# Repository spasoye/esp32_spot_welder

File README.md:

# ESP32 DIY Spot Welder Controller

A precision pulse controller for building a spot welder from a microwave oven transformer (MOT). Features configurable timing, safety controls, and an intuitive rotary encoder interface.

## ⚡ What It Does

Converts a dangerous MOT into a safe, controllable spot welder for battery tab welding, metalworking projects, and electronics repair. The ESP32 generates precise current pulses while the solid-state relay handles the high-power switching safely.

## 🎯 Key Features

- **Configurable pulse timing** - Adjust ON/OFF duration and pulse count via rotary encoder
- **Safety-critical design** - Software-controlled SSR prevents accidental activation
- **Real-time feedback** - 16x2 LCD shows current settings and pulse count
- **Precise control** - Microsecond-level timing for consistent welds
- **Easy interface** - Rotary encoder for parameter adjustment without recompilation

## 🔧 Hardware Requirements

- ESP32 development board
- 16x2 I2C LCD display (HD44780-compatible)
- Rotary encoder
- Solid state relay (SSR) rated for mains voltage
- Microwave oven transformer (MOT)
- Foot pedal or momentary switch (trigger)
- Power supply (3.3V/5V for ESP32, mains for MOT)

**⚠️ Safety Warning:** MOTs output extremely high current (1000+ amps). Improper construction can be lethal. Only attempt if you understand high-voltage/high-current safety practices.

## 📐 Circuit Diagram

Schematics available in `/kicad` directory. Key connections:
- ESP32 GPIO → SSR control input
- SSR output → MOT primary winding
- Rotary encoder → ESP32 GPIO (with debouncing)
- LCD → ESP32 I2C bus
- Trigger switch → ESP32 GPIO (with pull-up)

## 🚀 Building & Flashing

### Prerequisites
- ESP-IDF v4.x or later
- Git

### Clone with submodules
```bash
git clone --recursive https://github.com/spasoye/esp32_spot_welder.git
cd esp32_spot_welder/firmware
```

### Build and flash (choose one method)

**Using idf.py (recommended):**
```bash
idf.py build
idf.py -p /dev/ttyUSB0 flash monitor
```

**Using legacy make:**
```bash
make all -j8
make flash
```

## 🎮 Operation

1. **Power on** - LCD displays current pulse settings
2. **Adjust parameters** using rotary encoder:
   - Pulse ON time (milliseconds)
   - Pulse OFF time (milliseconds)  
   - Number of pulses (1-10)
3. **Press trigger** (foot pedal/switch) - LED indicates welding in progress
4. **Release trigger** - System returns to idle state

## 📊 Technical Highlights

- **ESP-IDF framework** - Professional-grade embedded development
- **Hardware timer control** - Precise pulse generation independent of task scheduling
- **Interrupt-driven encoder** - Responsive UI without polling overhead
- **I2C LCD library** - Clean abstraction using [esp32-i2c-lcd1602](https://github.com/DavidAntliff/esp32-i2c-lcd1602)
- **State machine design** - Safe mode transitions prevent accidental activation

## 📝 Configuration

Edit `main/config.h` to customize:
- GPIO pin assignments
- Default pulse parameters
- LCD I2C address
- Encoder sensitivity

## 🔗 Dependencies

- [esp32-i2c-lcd1602](https://github.com/DavidAntliff/esp32-i2c-lcd1602) - LCD display driver (included as submodule)

See [CHANGELOG.md](CHANGELOG.md) for version history.

## ⚠️ Disclaimer

This project involves high voltage and high current electricity. The author assumes no responsibility for injury, death, or property damage resulting from construction or use of this device. Build at your own risk.

## 📄 License

MIT License - See LICENSE file for details

---

**Built by Ivan Spasić** | [Portfolio](https://spas-tech.hr) | [GitHub](https://github.com/spasoye)

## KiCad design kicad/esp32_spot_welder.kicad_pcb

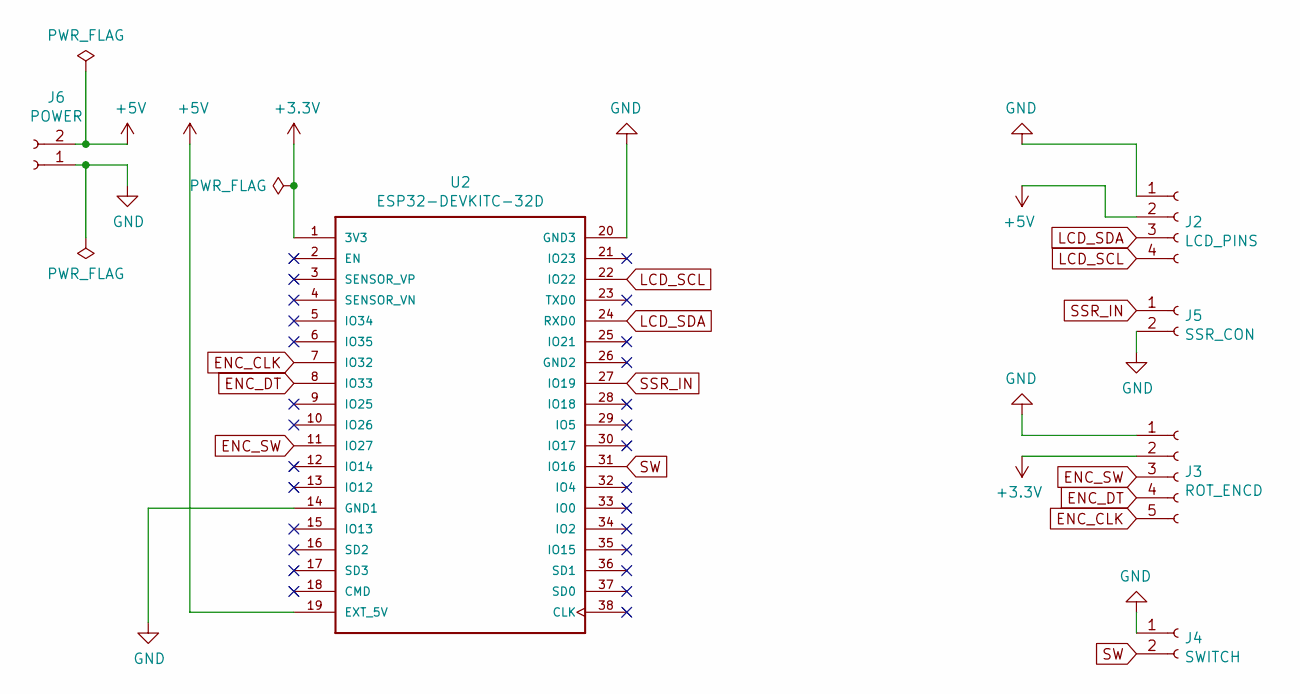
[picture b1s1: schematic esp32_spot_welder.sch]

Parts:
J2: LCD_PINS; PinHeader_1x04_P2.00mm_Vertical
J3: ROT_ENCD; PinHeader_1x05_P2.00mm_Vertical
J4: SWITCH; TerminalBlock_Philmore_TB132_1x02_P5.00mm_Horizontal
J5: SSR_CON; TerminalBlock_Philmore_TB132_1x02_P5.00mm_Horizontal
J6: POWER; TerminalBlock_Philmore_TB132_1x02_P5.00mm_Horizontal
U2: ESP32-DEVKITC-32D; MODULE_ESP32-DEVKITC-32D

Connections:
+3V3: J3.2, U2.1 (3V3)
+5V: J2.2, J6.2, U2.19 (EXT_5V)
ENC_CLK: J3.5, U2.7 (IO32)
ENC_DT: J3.4, U2.8 (IO33)
ENC_SW: J3.3, U2.11 (IO27)
GND: J2.1, J3.1, J4.1, J5.2, J6.1, U2.14 (GND1), U2.20 (GND3)
LCD_SCL: J2.4, U2.22 (IO22)
LCD_SDA: J2.3, U2.24 (RXD0)
SSR_IN: J5.1, U2.27 (IO19)
SW: J4.2, U2.31 (IO16)

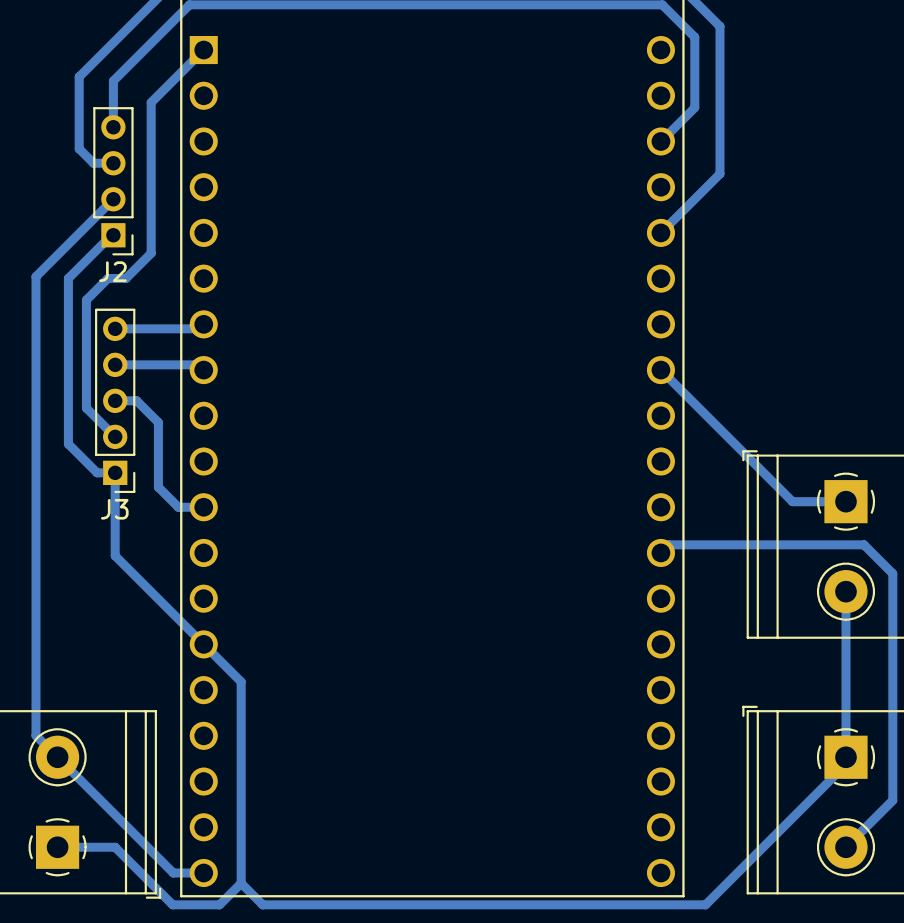
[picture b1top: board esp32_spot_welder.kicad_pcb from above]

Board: 2 copper layers, 6 parts (0 on the bottom side), 10 nets.

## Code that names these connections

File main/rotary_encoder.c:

#include <math.h>
#include <driver/gpio.h>
#include "freertos/FreeRTOS.h"
#include "freertos/task.h"
#include "freertos/queue.h"
#include "rotary_encoder.h"

#include "lcd.h"

#define ENC_CLK     GPIO_NUM_32
#define ENC_DT      GPIO_NUM_33
#define ENC_SW      27

static QueueHandle_t p_encoder_queue = NULL;
static int16_t duration = 100;

/**
 * @brief  Rotary encoder interrupt service routine. 
 * @note   Debounce protocol should be done here.
 * @param  *arg: pin that triggered the interrupt.
 * @retval None
 */
static void IRAM_ATTR encoder_isr_handler(void *arg);

/**
 * @brief  Task routine that haqndles interrupt events.
 * @note   None.
 * @param  *arg: task arguments. None in this case.
 * @retval None
 */
static void rotary_encoder_task(void *arg);

uint8_t rotary_encoder_init(void)
{
    gpio_config_t io_conf;
    uint8_t ret = 1;

    io_conf.intr_type = GPIO_PIN_INTR_DISABLE;
    io_conf.mode = GPIO_MODE_INPUT;
    io_conf.pin_bit_mask = (1ULL<<ENC_CLK);
    io_conf.pull_down_en = GPIO_PULLDOWN_DISABLE;
    io_conf.pull_up_en = GPIO_PULLDOWN_DISABLE;
    gpio_config(&io_conf);

    io_conf.intr_type = GPIO_PIN_INTR_NEGEDGE;
    io_conf.pin_bit_mask = (1ULL<<ENC_DT);
    io_conf.mode = GPIO_MODE_INPUT;
    io_conf.pull_up_en = GPIO_PULLDOWN_DISABLE;
    io_conf.pull_down_en = GPIO_PULLDOWN_DISABLE;
    gpio_config(&io_conf);

    io_conf.intr_type = GPIO_PIN_INTR_NEGEDGE;
    io_conf.pin_bit_mask = (1<<ENC_SW);
    io_conf.mode = GPIO_MODE_INPUT;
    io_conf.pull_up_en = GPIO_PULLDOWN_DISABLE;
    io_conf.pull_down_en = GPIO_PULLDOWN_DISABLE;
    gpio_config(&io_conf);

    gpio_install_isr_service(0);
    gpio_isr_handler_add(ENC_CLK, encoder_isr_handler, (void*)ENC_CLK);
    gpio_isr_handler_add(ENC_DT, encoder_isr_handler, (void*)ENC_DT);
    gpio_isr_handler_add(ENC_SW, encoder_isr_handler, (void*)ENC_SW);

    p_encoder_queue = xQueueCreate(1, sizeof(encoder_event_t));

    ret = (pdPASS ==xTaskCreatePinnedToCore(rotary_encoder_task, "rotary_encoder_task", 2048, NULL, 10, NULL, 0)) ? 0 : 1;

    return ret;
}

void rotary_encoder_int_disable(void)
{
    gpio_intr_disable(ENC_CLK);
    gpio_intr_disable(ENC_DT);
    gpio_intr_disable(ENC_SW);
}

void rotary_encoder_int_enable(void)
{
    gpio_intr_enable(ENC_CLK);
    gpio_intr_enable(ENC_DT);
    gpio_intr_enable(ENC_SW);
}

static void rotary_encoder_task(void *arg)
{
    encoder_event_t encod_val;
    uint8_t digit_pos = 0;
    uint8_t cursor_pos[] = {4, 1};

    lcd_set_dur(duration);
    lcd_user_pointer(cursor_pos);

    while(true)
    {
        if (xQueueReceive(p_encoder_queue, &encod_val, portMAX_DELAY))
        {
            printf("Interrupt from %d\n", encod_val);
            switch (encod_val)
            {
            case CLICK:
                digit_pos = (digit_pos+1)%4;
                cursor_pos[0] = 4-digit_pos;
                printf("Digit: %d\n", digit_pos);
                lcd_user_pointer(cursor_pos);
                break;

            case CCW:
                printf("-\n");
                duration = duration - pow(10, digit_pos);
                break;

            case CW:
                printf("+\n");
                duration = duration + pow(10, digit_pos);
                break;

            default:
                break;
            }
            
            // Value can't be smaller than 0;
            if (duration < 0)
            {
                duration = 0;
            }

            // Value can't be larger than 5000 ms.
            if (duration > 5000)
            {
                duration = 5000;
            }

            lcd_set_dur(duration);
            vTaskDelay(60/portTICK_PERIOD_MS);
            gpio_intr_enable(ENC_DT);
            gpio_intr_enable(ENC_SW);
        }
    }
}

uint16_t rotary_encoder_get_duration(void)
{
    return duration;
}

static void IRAM_ATTR encoder_isr_handler(void *arg)
{
    encoder_event_t val;
    
    // TODO: Fix debounce issue.

    // Disable interrupts until the handling is done.
    gpio_intr_disable(ENC_DT);
    gpio_intr_disable(ENC_SW);

    uint8_t a = gpio_get_level(ENC_CLK);
    uint8_t b = gpio_get_level(ENC_DT);
    
    if ((int32_t*)arg == ENC_SW)
    {
        val = CLICK;
    }
    else if (a == b)
    {
        val = CCW;
    }
    else
    {
        val = CW;
    }
    
    xQueueSendFromISR(p_encoder_queue, &val, NULL);
}

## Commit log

2020-03-15 Using binary semaphore instead of queue
2020-03-18 Debounce after pulse
2020-03-18 Interrupt on falling edge
2020-03-28 Added esp32-smbus DavidAntliff repo as submodule
2020-03-28 Added esp32-i2c-lcd1602 David's repo as submodule
2020-04-01 Updated .gitignore
2020-04-02 Started LCD implementation
2020-04-02 Implemented lcd initialization and value setting
2020-04-02 changed format to 5 digits
2020-04-02 Rotary encoder WIP
2020-04-03 Implemented rotary encoder WIP
2020-04-04 Fixed encoder triggering
2020-04-04 Implemented lcd_user_pointer function
2020-04-04 Changing the duration value using encoder
2020-04-05 Limit to duration value
2020-04-05 Added comments
2020-04-05 Minimum duration limit
2020-04-05 Implemented duration return function
2020-04-05 Refactoring and comments
2020-04-08 Implemented rotart encoder interrupt disable/enable functions
2020-04-12 fixing debounce issue WIP
2020-04-12 Added sch and pcb
2020-04-18 kicad fix
2020-04-18 Implemented duration warning
2020-06-27 enabled build using idf.py
2020-06-27 build in readme
2020-06-27 kicad changes
2020-07-02 separeted firmware and pcb
2020-07-14 kicad stuff to gitignore
2020-07-14 readme to root
2020-07-14 tidy
2020-07-14 kicad changed
2020-07-14 .gitignore update
2020-07-15 Click separate handler
2020-07-15 duration warning fix
2020-07-15 rotation debounce WIP
2020-07-19 removed unnecessary stuf
2020-07-19 Better CW/CCW detection
2020-07-19 moved lcd and rot_enc to components
2020-07-20 interface minor changes
2020-07-20 Switch and MOT ctrl to separate component
2020-07-20 define change
2020-07-21 renamed rotary_encoder to interface
2020-07-21 Implemented short and long press
2020-07-21 implemented set functions
2020-07-21 Implementing properties interface WIP
2020-07-22 Implemented multiple properties interface
2020-07-23 fixed ssr control
2020-07-24 fixed rot_encd debounce issue
2020-07-24 updated kicad
2020-08-01 added CHANGELOG.md
2020-08-02 Updated CHANGELOG
2020-09-28 Removed unnecessary stuff
2020-09-28 interface_get_Val comment
2020-10-06 v0.2.0 picture
2020-10-14 test
2026-02-02 Revise README.md for clarity and detail on ESP32 DIY Spot Welder features, usage, and safety warnings
